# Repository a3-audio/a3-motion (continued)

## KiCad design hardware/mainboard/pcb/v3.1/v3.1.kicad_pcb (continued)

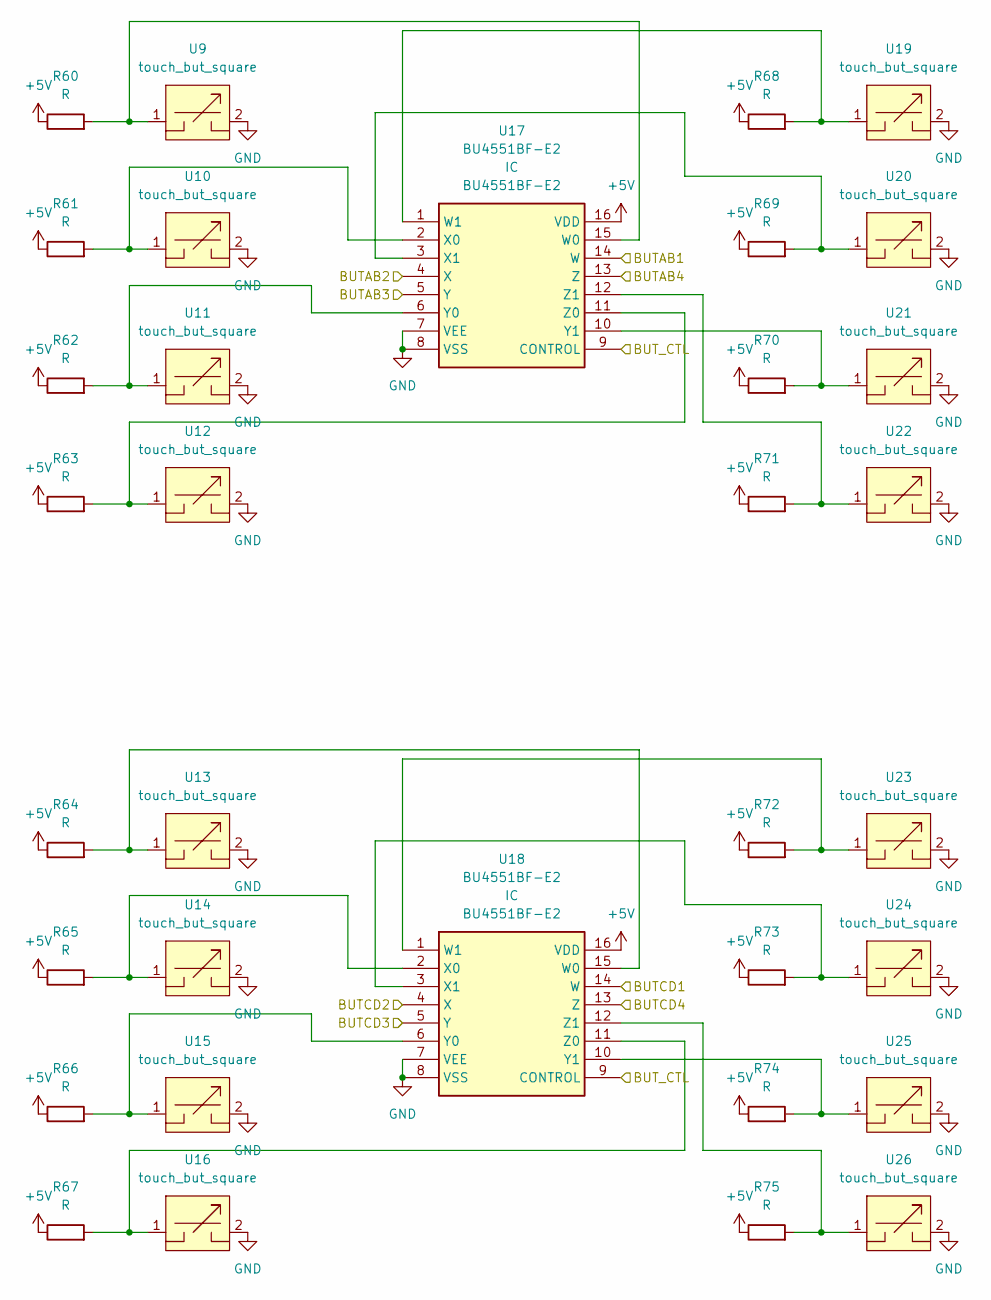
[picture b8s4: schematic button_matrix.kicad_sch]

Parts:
R60, R61, R62, R63, R64, R65, R66, R67, R68, R69, R70, R71, R72, R73, R74, R75: R; R_1206_3216Metric_Pad1.30x1.75mm_HandSolder
U9, U10, U11, U12, U13, U14, U15, U16, U19, U20, U21, U22, U23, U24, U25, U26: touch_but_square; But_Velo_Rec_1
U17, U18: BU4551BF-E2; SOIC127P620X171-16N; Mouser Part Number 755-BU4551BF-E2

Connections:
+5V: R60.1, R61.1, R62.1, R63.1, R64.1, R65.1, R66.1, R67.1, R68.1, R69.1, R70.1, R71.1, R72.1, R73.1, R74.1, R75.1, U17.16 (VDD), U18.16 (VDD); also elsewhere on the board
/Button round/BUTAB1: U17.14 (W); also elsewhere on the board
/Button round/BUTAB2: U17.4 (X); also elsewhere on the board
/Button round/BUTAB3: U17.5 (Y); also elsewhere on the board
/Button round/BUTAB4: U17.13 (Z); also elsewhere on the board
/Button round/BUTCD1: U18.14 (W); also elsewhere on the board
/Button round/BUTCD2: U18.4 (X); also elsewhere on the board
/Button round/BUTCD3: U18.5 (Y); also elsewhere on the board
/Button round/BUTCD4: U18.13 (Z); also elsewhere on the board
/Button round/BUT_CTL: U17.9 (CONTROL), U18.9 (CONTROL); also elsewhere on the board
GND: U9.2, U10.2, U11.2, U12.2, U13.2, U14.2, U15.2, U16.2, U17.7 (VEE), U17.8 (VSS), U18.7 (VEE), U18.8 (VSS), U19.2, U20.2, U21.2, U22.2, U23.2, U24.2, U25.2, U26.2; also elsewhere on the board
unnamed: R60.2, U9.1, U17.15 (W0)
unnamed: R61.2, U10.1, U17.2 (X0)
unnamed: R62.2, U11.1, U17.6 (Y0)
unnamed: R63.2, U12.1, U17.11 (Z0)
unnamed: R64.2, U13.1, U18.15 (W0)
unnamed: R65.2, U14.1, U18.2 (X0)
unnamed: R66.2, U15.1, U18.6 (Y0)
unnamed: R67.2, U16.1, U18.11 (Z0)
unnamed: R68.2, U17.1 (W1), U19.1
unnamed: R69.2, U17.3 (X1), U20.1
unnamed: R70.2, U17.10 (Y1), U21.1
unnamed: R71.2, U17.12 (Z1), U22.1
unnamed: R72.2, U18.1 (W1), U23.1
unnamed: R73.2, U18.3 (X1), U24.1
unnamed: R74.2, U18.10 (Y1), U25.1
unnamed: R75.2, U18.12 (Z1), U26.1

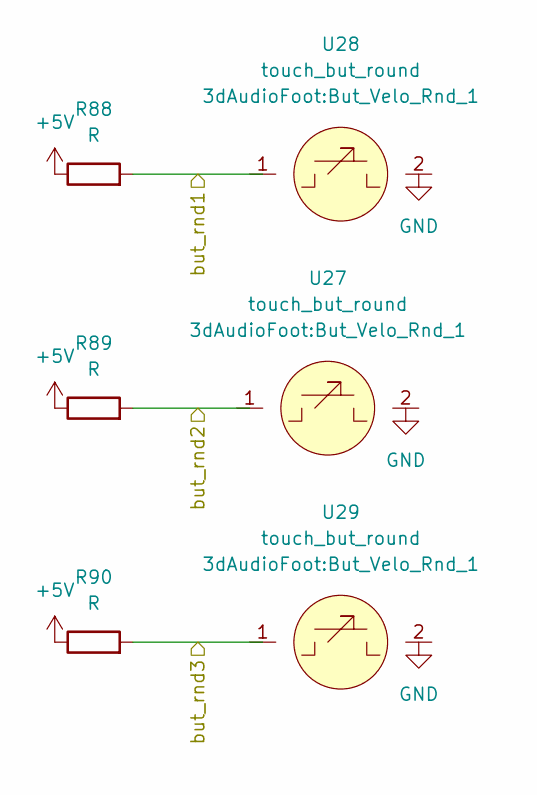
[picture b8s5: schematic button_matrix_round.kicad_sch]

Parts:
R88, R89, R90: R; R_1206_3216Metric_Pad1.30x1.75mm_HandSolder
U27, U28, U29: touch_but_round; But_Velo_Rnd_1

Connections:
+5V: R88.1, R89.1, R90.1; also elsewhere on the board
BR1: R88.2; also elsewhere on the board
BR2: R89.2; also elsewhere on the board
BR3: R90.2; also elsewhere on the board

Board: 2 copper layers, 159 parts (0 on the bottom side), 162 nets, no tracks yet.

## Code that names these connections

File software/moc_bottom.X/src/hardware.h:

/*
 * hardware.h
 *
 * Created: 17/03/2022 13:06:41
 *  Author: tirii
 */ 


#ifndef HARDWARE_H_
#define HARDWARE_H_
#include <avr/io.h>
#define F_CPU 20000000UL

#define BUR1_PT     PORTA	//PA4
#define BUR1__BP	PIN4_bp
#define BUR1__BM	PIN4_bm

#define BUR2_PT     PORTB	//PB2
#define BUR2__BP	PIN2_bp
#define BUR2__BM	PIN2_bm

#define ENC1_A_PT	PORTA	//PA5
#define ENC1_A_BP	PIN5_bp
#define ENC1_A_BM	PIN5_bm

#define ENC1_B_PT	PORTA	//PA6
#define ENC1_B_BP	PIN6_bp
#define ENC1_B_BM	PIN6_bm

#define ENC1_SW_PT	PORTA	//PA7
#define ENC1_SW_BP	PIN7_bp
#define ENC1_SW_BM	PIN7_bm

#define ENC2_A_PT	PORTB	//PB5
#define ENC2_A_BP	PIN5_bp
#define ENC2_A_BM	PIN5_bm

#define ENC2_B_PT	PORTB	//PB4
#define ENC2_B_BP	PIN4_bp
#define ENC2_B_BM	PIN4_bm

#define ENC2_SW_PT	PORTB	//PB3
#define ENC2_SW_BP	PIN3_bp
#define ENC2_SW_BM	PIN3_bm

#define ENC3_SW_PT	PORTA	//PA2
#define ENC3_SW_BP	PIN2_bp
#define ENC3_SW_BM	PIN2_bm

#define ENC4_SW_PT	PORTC	//PC2
#define ENC4_SW_BP	PIN2_bp
#define ENC4_SW_BM	PIN2_bm

#define TWI_SDA_PT	PORTB	//PB1
#define TWI_SDA_BP	PIN1_bp
#define TWI_SDA_BM	PIN1_bm

#define TWI_SCL_PT	PORTB	//PB0
#define TWI_SCL_BP	PIN0_bp
#define TWI_SCL_BM	PIN0_bm

#define LED_SHU_PT	PORTC	//PC3
#define LED_SHU_BP	PIN3_bp
#define LED_SHU_BM	PIN3_bm

#define LED_SHD_PT	PORTA	//PA1
#define LED_SHD_BP	PIN1_bp
#define LED_SHD_BM	PIN1_bm

#define LED_SHC_PT	PORTA	//PA3
#define LED_SHC_BP	PIN3_bp
#define LED_SHC_BM	PIN3_bm

#define POS_LEDS1B	0    // 1
#define POS_LEDS1R	1    // 2
#define POS_LEDS1G	2    // 3
#define POS_LEDS2B	3    // 4
#define POS_LEDS2R	4    // 5
#define POS_LEDS2G	5    // 6
#define POS_LEDS3B	6    // 7
#define POS_LEDS3R	7    // 8
#define POS_LEDS3G	8    // 9
#define POS_LEDS4B	9    // 10
#define POS_LEDS4R	10   // 11
#define POS_LEDS4G	11   // 12
#define POS_LEDS5B	12   // 13
#define POS_LEDS5R	13   // 14
#define POS_LEDS5G	14   // 15
#define POS_LEDS6B	16   // 16
#define POS_LEDS6R	17   // 17
#define POS_LEDS6G	18   // 18
#define POS_LEDS7B	19   // 19
#define POS_LEDS7R	20   // 20
#define POS_LEDS7G	21   // 21
#define POS_LEDS8B	22   // 22
#define POS_LEDS8R	23   // 23
#define POS_LEDS8G	24   // 24
#define POS_LEDS9B	25   // 25
#define POS_LEDS9R	26   // 26
#define POS_LEDS9G	27   // 27
#define POS_LEDS10B	28   // 28
#define POS_LEDS10R	29   // 29
#define POS_LEDS10G 30   // 30
#define POS_LEDS11B	32   // 31
#define POS_LEDS11R	33   // 32
#define POS_LEDS11G	34   // 33
#define POS_LEDS12B	35   // 34
#define POS_LEDS12R	36   // 35
#define POS_LEDS12G	37   // 36
#define POS_LEDS13B	38   // 37
#define POS_LEDS13R	39   // 38
#define POS_LEDS13G	40   // 39
#define POS_LEDS14B	41   // 40
#define POS_LEDS14R	42   // 41
#define POS_LEDS14G	43   // 42
#define POS_LEDS15B	44   // 43
#define POS_LEDS15R	45   // 44
#define POS_LEDS15G	46   // 45
#define POS_LEDS16B	48   // 46
#define POS_LEDS16R	49   // 47
#define POS_LEDS16G	50   // 48
#define POS_LEDS17B	51   // 49
#define POS_LEDS17R	52   // 50
#define POS_LEDS17G	53   // 51
#define POS_LEDS18B	54   // 52
#define POS_LEDS18R	55   // 53
#define POS_LEDS18G	56   // 54
#define POS_LEDS19B	57   // 55
#define POS_LEDS19R	58   // 56
#define POS_LEDS19G	59   // 57







#endif /* HARDWARE_H_ */

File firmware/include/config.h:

#ifndef A3_MOTION_FIRMWARE_CONFIG_H
#define A3_MOTION_FIRMWARE_CONFIG_H

#include <Arduino.h>
#include "pot_config.h"

constexpr uint8_t LED_PIN = 14;
constexpr uint8_t NUMPIXELS = 44;

// How much the 44 key LEDs may draw together, as led_budget.h estimates it
// -- the datasheet's figures, not what a meter would read. They hang on the
// USB 5 V of a USB 2.0 port on the NUC.
//
// Set from what the app really shows (a3-motion-ui#21): its own copy of the
// estimate logged every new peak while the maintainer played a full session
// on 2026-09-26. The highest was 1144, the resting picture -- the idle colour
// lights every key, and playing changes colours rather than adding light.
// That picture has run on this port for months, so it is known to be safe;
// the budget sits about 14 % above it. Normal use is never dimmed, and full
// white on every key (about 2700 by this estimate) is halved.
//
// Not measured with a meter: if one ever is, the per-colour figure in
// led_budget.h is what to calibrate, and this number with it.
constexpr uint32_t LED_BUDGET_MA = 1300;

constexpr uint8_t BUTTON_MUX_COUNT = 5;
constexpr uint8_t MUX_CHANNEL_COUNT = 8;
constexpr uint8_t EXTRA_BUTTON_COUNT = 4;
constexpr uint8_t MATRIX_BUTTON_COUNT = (BUTTON_MUX_COUNT * MUX_CHANNEL_COUNT) + EXTRA_BUTTON_COUNT;
constexpr uint8_t ENCODER_COUNT = 8;
constexpr uint8_t SELECT_PIN_COUNT = 3;
constexpr uint8_t LED_MATRIX_ROWS = 6;
constexpr uint8_t LED_MATRIX_COLS = 10;
constexpr uint8_t LED_MATRIX_A3_START_ROW = 1;
constexpr uint8_t LED_MATRIX_A3_START_COL = 1;
constexpr uint8_t LED_MATRIX_A3_ROW_COUNT = 5;
constexpr uint8_t LED_MATRIX_A3_COL_COUNT = 9;

constexpr uint8_t BUTTON_RELEASE_DELAY_MS = 5;
constexpr uint8_t MUX_SETTLE_DELAY_US = 12;
constexpr uint32_t INPUT_SCAN_INTERVAL_US = 450;
constexpr uint32_t CMD_PROCESS_BUDGET_US = 650;
constexpr uint32_t LED_SHOW_MIN_INTERVAL_US = 0;
constexpr uint8_t PROTOCOL_PAYLOAD_TIMEOUT_MS = 3;
// Number of quadrature transitions per mechanical encoder detent.
// Most common mechanical encoders are 4; set to 2 if movement feels under-reported.
constexpr uint8_t ENCODER_COUNTS_PER_DETENT = 4;

constexpr uint8_t MUX_S0 = 39;
constexpr uint8_t MUX_S1 = 38;
constexpr uint8_t MUX_S2 = 48;

constexpr uint8_t MUX_0_GPIO = 41;//MAA01 Button20 bis 51
constexpr uint8_t MUX_1_GPIO = 42;//MAA23 Button22 bis 53
constexpr uint8_t MUX_2_GPIO = 40;//MAA45 Button24 bis 55
constexpr uint8_t MUX_3_GPIO = 21;//MAA67 Button26 bis 57
constexpr uint8_t MUX_4_GPIO = 47;//MAA89 Button28 bis 59
constexpr uint8_t MUX_5_GPIO = 2;//MA  Button00,01 ENC1 und ENC2
constexpr uint8_t MUX_6_GPIO = 15;//MB ENC5 
constexpr uint8_t MUX_7_GPIO = 8;//MC ENC3,ENC6,ENC7 
constexpr uint8_t MUX_8_GPIO = 9;//MD Button09,19 und ENC4,ENC8

constexpr uint8_t ENCODER_1A_PIN = 6;
constexpr uint8_t ENCODER_2A_PIN = 7;
constexpr uint8_t ENCODER_3A_PIN = 11;
constexpr uint8_t ENCODER_4A_PIN = 12;
constexpr uint8_t ENCODER_5A_PIN = 5;
constexpr uint8_t ENCODER_6A_PIN = 18;
constexpr uint8_t ENCODER_7A_PIN = 10;
constexpr uint8_t ENCODER_8A_PIN = 13;

constexpr uint8_t POT_1_PIN = 4;
constexpr uint8_t POT_2_PIN = 16;
constexpr uint8_t POT_3_PIN = 17;
constexpr uint8_t POT_4_PIN = 3;

constexpr uint8_t SELECT_PINS[SELECT_PIN_COUNT] = {
  MUX_S0,
  MUX_S1,
  MUX_S2
};

constexpr uint8_t MUX_PINS[9] = {
  MUX_0_GPIO,
  MUX_1_GPIO,
  MUX_2_GPIO,
  MUX_3_GPIO,
  MUX_4_GPIO,
  MUX_5_GPIO,
  MUX_6_GPIO,
  MUX_7_GPIO,
  MUX_8_GPIO
};

constexpr uint8_t ENCODER_A_PINS[ENCODER_COUNT] = {
  ENCODER_1A_PIN, ENCODER_2A_PIN, ENCODER_3A_PIN, ENCODER_4A_PIN,
  ENCODER_5A_PIN, ENCODER_6A_PIN, ENCODER_7A_PIN, ENCODER_8A_PIN
};

constexpr uint8_t POT_PINS[POT_MUX_COUNT] = {
  POT_1_PIN, POT_2_PIN, POT_3_PIN, POT_4_PIN
};

// Physical daisy-chain order on the board.
// First addressable LED is 09, last is 00.
constexpr uint8_t LED_PHYSICAL_ORDER[NUMPIXELS] = {
  9, 19, 29, 39, 49, 59,
  58, 48, 38, 28,
  27, 37, 47, 57,
  56, 46, 36, 26,
  25, 35, 45, 55,
  54, 44, 34, 24,
  23, 33, 43, 53,
  52, 42, 32, 22,
  21, 31, 41, 51,
  50, 40, 30, 20, 10, 0
};

constexpr int8_t LED_MATRIX[LED_MATRIX_ROWS][LED_MATRIX_COLS] = {
  { 43, -1, -1, -1, -1, -1, -1, -1, -1, 0 },
  { 42, -1, -1, -1, -1, -1, -1, -1, -1, 1 },
  { 41, 34, 33, 26, 25, 18, 17, 10, 9, 2 },
  { 40, 35, 32, 27, 24, 19, 16, 11, 8, 3 },
  { 39, 36, 31, 28, 23, 20, 15, 12, 7, 4 },
  { 38, 37, 30, 29, 22, 21, 14, 13, 6, 5 }
};

#endif

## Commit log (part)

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2023-05-11 migrate v2 motion controller to new repository
2023-05-11 add MotionControllerUI submodule
2023-07-24 remove manjaro-arm platform config, add a3-motion-ui submodule
2023-07-24 add license
2023-07-24 Update LICENSE
2023-07-24 add license via reuse
2023-07-24 deleteold License file
2023-07-24 set reuse copiright and licenses
2023-07-24 change to CC-BY-SA-4.0
2023-07-26 add libserial and gpiod packages to setup instructions
2023-07-27 add system buttons as teensy inputs, send B16-19
2023-07-27 fix system button pins and pullup
2023-07-27 fix encoders, send increment only
2023-07-27 receive button leds as BL
2023-07-27 enable pull-down on analog mux pin, decrease hysteresis threshold
2023-07-27 add .pio project folders to gitignore
2023-07-28 bump ui submodule version
2023-07-28 add v03-casedesign
2023-08-08 invert low/high for rec/shift/tap buttons
2023-08-08 consider encoder step size 4
2023-08-18 change LED pin order to match buttons
2023-08-28 read tap button via isr and send time stamps
2023-08-29 don't wait for serial connection in init
2023-08-29 count all presses again, don't check release count
2023-08-29 set all neopixels for pad leds to black on init
2023-08-29 consolidate/fix receiving of LEDs via serial
2023-09-02 license added
2023-09-02 corrections
2023-09-03 add hardware from a3-system repo
2023-09-04 debounce pads
2023-09-04 set debounce time for pads to 30 ms, tested with v1
2023-10-02 add freeCAD design
2023-10-04 cleaned freecad > technical drawing
2023-10-04 no edits
2023-10-08 button matrix
2023-10-08 freecad next to kicad
2023-10-08 top encoder und zechdraw
2023-10-08 pcb in freecad aligned
2023-10-08 align top encoder
2023-10-08 Version update
2023-10-08 rubberpad draft
2023-10-08 pcb cut off
2023-10-08 good progress
2023-10-08 update to 74hc4053aft
2024-01-14 cleanup repo
2024-01-14 cleanup
2024-01-15 started placement
2024-02-11 pcb main fertig
2024-03-27 just a commit to reassemble changes of the past month
2024-04-04 finished top and main PCB
2024-04-06 generated gerber files v31
2024-05-25 checked licensing
2024-07-10 correct licenses
2025-01-11 cleaned
2025-08-21 after move to kicad 9
2025-09-25 changed workplace
2025-09-25 changed workplace2
2025-09-25 change workplace3
2025-09-25 changed gitignore
2025-09-25 started new projects
2025-09-25 setup workspace
2026-01-24 test
2026-02-13 before ki
2026-02-25 clean up
2026-02-25 clean up merge sym libs
2026-02-26 new case layout
2026-03-01 finished schematic
2026-03-01 cleanup led driver
2026-03-01 add pcb makro and freecad pcb design
2026-03-01 created submodule for enc pot mix
2026-03-04 new layout mx
2026-03-04 more space
2026-03-04 add hands
2026-03-05 changing labels
2026-03-05 changiong labels again
2026-03-07 finished pcb motion.
2026-03-07 finished design
2026-05-16 neue encoder definition und buttons
2026-05-16 team.md hinzugefuegt
2026-05-16 easter egg hoffentlich klappt das
2026-05-18 usart protocoll implementiert
2026-05-19 Flex Firnmware rocks git add -A!
2026-05-20 led communication
2026-05-20 firmware optimization
2026-05-20 Tune poti/encoder responsiveness baseline
2026-05-20 Improve firmware loop throughput and LED flush scheduling
2026-05-20 optimize firmware / better values / better performance
2026-05-20 move host.py
